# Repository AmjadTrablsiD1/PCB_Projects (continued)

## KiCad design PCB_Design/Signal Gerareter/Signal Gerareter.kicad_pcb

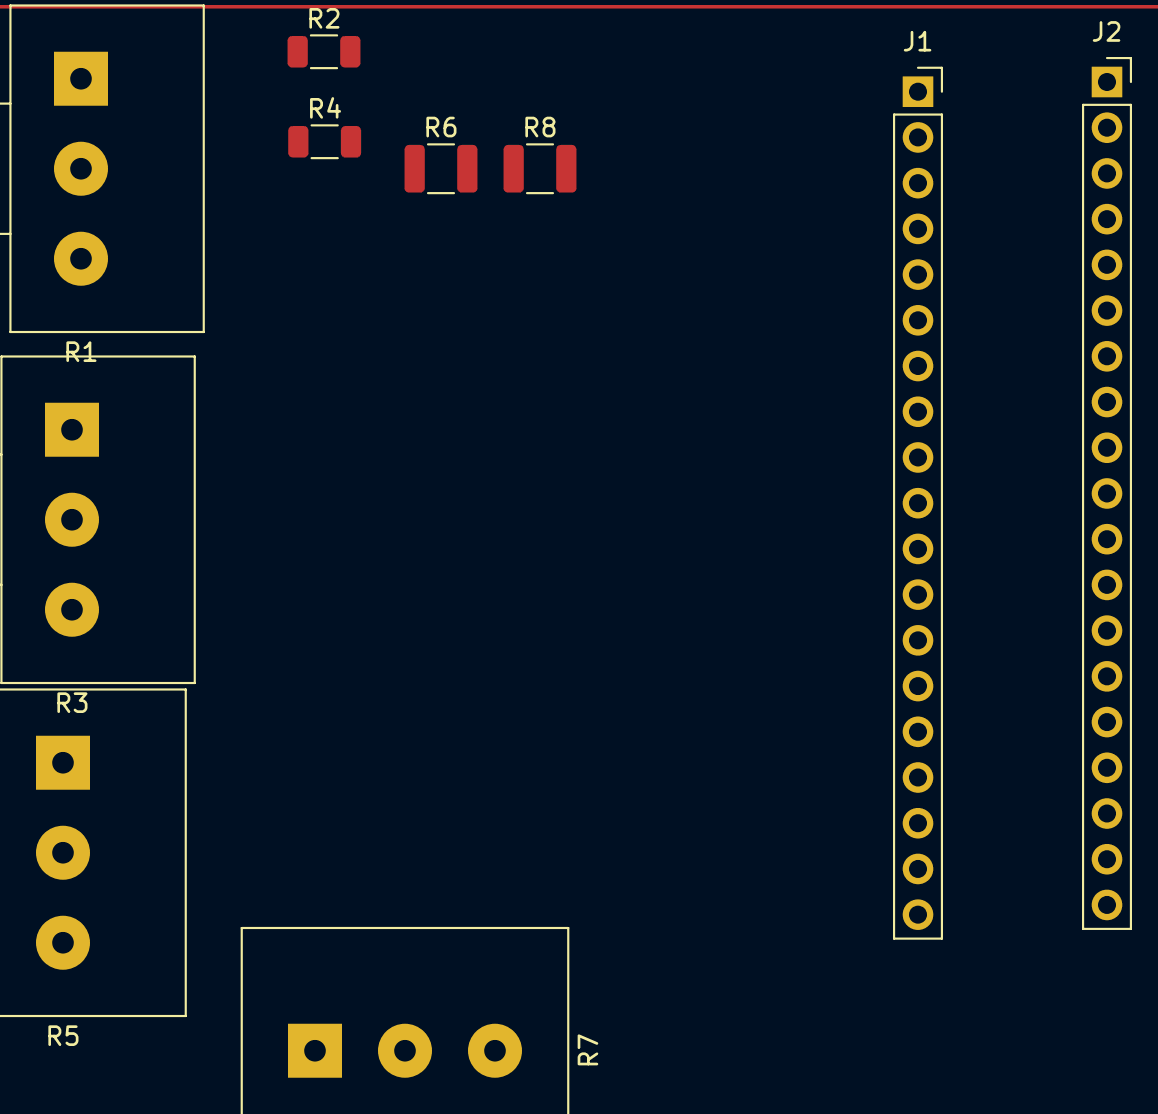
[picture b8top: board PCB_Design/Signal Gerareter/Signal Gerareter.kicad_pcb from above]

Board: 2 copper layers, 10 parts (0 on the bottom side), 5 nets, no tracks yet.

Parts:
J1, J2: Conn_01x19_Socket; PinSocket_1x19_P2.54mm_Vertical
R1, R3, R5, R7: R_Variable; Potentiometer_Alps_RK163_Single_Horizontal
R2, R4: 1k; R_1206_3216Metric
R6, R8: 1k; R_1210_3225Metric

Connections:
GND: R2.1, R4.1, R6.1, R8.1
unnamed: R1.2, R2.2
unnamed: R5.2, R6.2
unnamed: R3.2, R4.2
unnamed: R7.2, R8.2

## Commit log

2025-02-16 commit
    new_Commit
2025-02-26 projects structure update
2025-02-27 klein update
2025-04-13 bearbeitung
2025-04-19 update
    design update
2025-08-30 new design
